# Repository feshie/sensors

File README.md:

sensors
=======
These feshie smarft sensors use an MCU (AVR) to interface to the actual sensors - and provide protocol buffer formatted data

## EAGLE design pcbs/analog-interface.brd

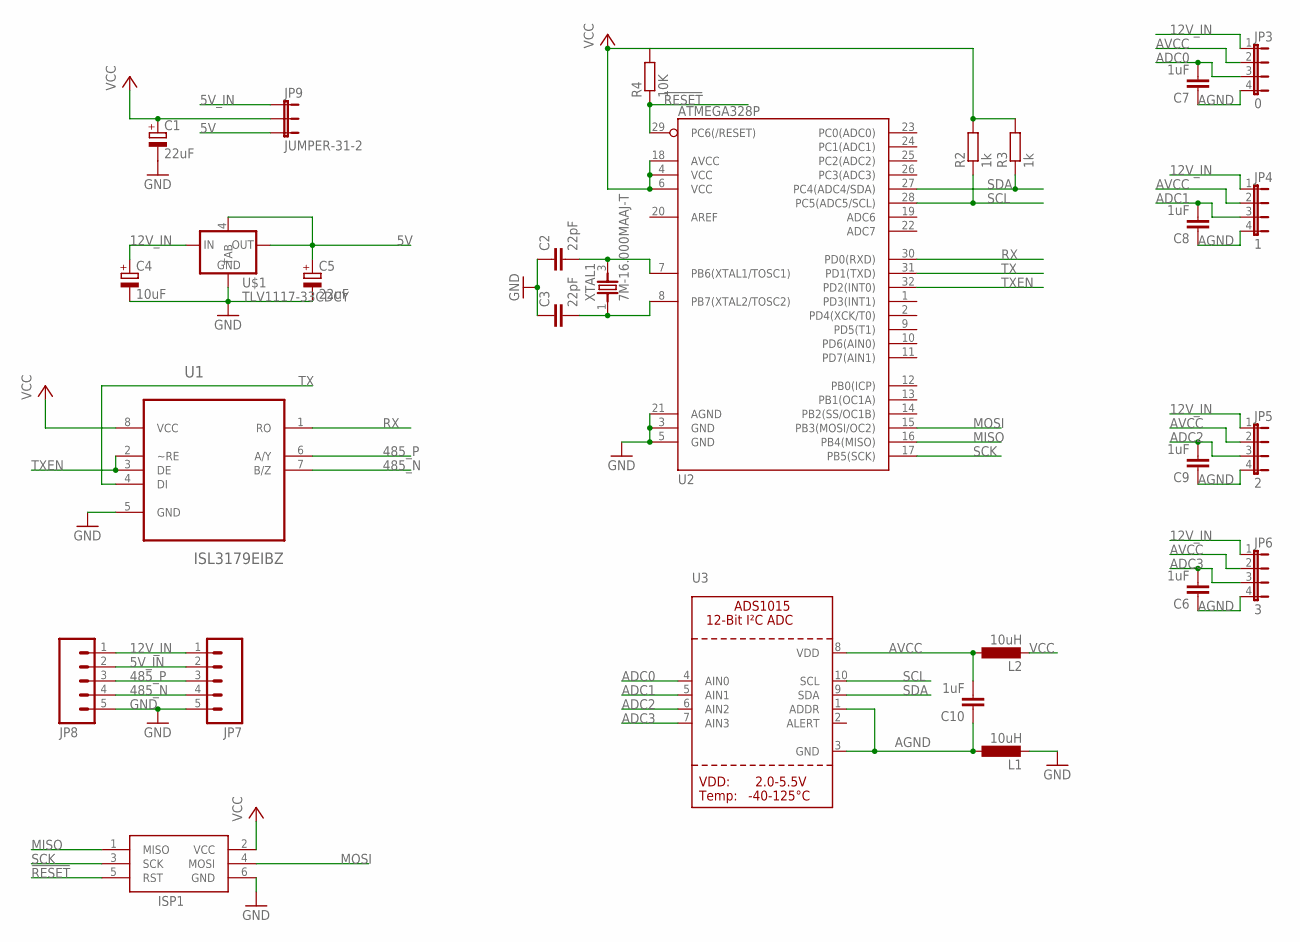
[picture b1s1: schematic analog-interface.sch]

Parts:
C1, C5: 22uF; A/3216-18R
C2, C3: 22pF; C0805
C4: 10uF; A/3216-18R
C6, C7, C8, C9, C10: 1uF; C0805
ISP1: AVRISP-6; AVRISP
JP3: 0; JP4
JP4: 1; JP4
JP5: 2; JP4
JP6: 3; JP4
JP7, JP8: M05PTH; 1X05
JP9: JUMPER-31-2; SJ_3_PASTE1&2
L1, L2: 10uH; L3216C
R2, R3: 1k; R0805
R4: 10K; R0805
U1: ISL3179EIBZ; SOIC127P600X175-8N
U2: ATMEGA328P; TQFP32-08
U3: ADC_ADS1015; MSOP10
U$1: TLV1117-33CDCY; SOT223
XTAL1: 7M-16.000MAAJ-T; TXC_7M-16.000MAAJ-T

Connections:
5V: C5.+, JP9.3, U$1.2 (OUT), U$1.4 (TAB)
5V_IN: JP7.2, JP8.2, JP9.1
12V_IN: C4.+, JP3.1, JP4.1, JP5.1, JP6.1, JP7.1, JP8.1, U$1.3 (IN)
485_N: JP7.4, JP8.4, U1.7 (B/Z)
485_P: JP7.3, JP8.3, U1.6 (A/Y)
!RESET: ISP1.5 (RST), R4.1, U2.29 (PC6(/RESET))
ADC0: C7.2, JP3.3, U3.4 (AIN0)
ADC1: C8.2, JP4.3, U3.5 (AIN1)
ADC2: C9.2, JP5.3, U3.6 (AIN2)
ADC3: C6.2, JP6.3, U3.7 (AIN3)
AGND: C6.1, C7.1, C8.1, C9.1, C10.1, JP3.4, JP4.4, JP5.4, JP6.4, L1.1, U3.1 (ADDR), U3.3 (GND)
AVCC: C10.2, JP3.2, JP4.2, JP5.2, JP6.2, L2.1, U3.8 (VDD)
GND: C1.-, C2.1, C3.1, C4.-, C5.-, ISP1.6 (GND), JP7.5, JP8.5, L1.2, U1.5 (GND), U2.3 (GND), U2.5 (GND), U2.21 (AGND), U$1.1 (GND)
MISO: ISP1.1 (MISO), U2.16 (PB4(MISO))
MOSI: ISP1.4 (MOSI), U2.15 (PB3(MOSI/OC2))
unnamed: C2.2, U2.7 (PB6(XTAL1/TOSC1)), XTAL1.3
unnamed: C3.2, U2.8 (PB7(XTAL2/TOSC2)), XTAL1.1
RX: U1.1 (RO), U2.30 (PD0(RXD))
SCK: ISP1.3 (SCK), U2.17 (PB5(SCK))
SCL: R2.1, U2.28 (PC5(ADC5/SCL)), U3.10 (SCL)
SDA: R3.1, U2.27 (PC4(ADC4/SDA)), U3.9 (SDA)
TX: U1.4 (DI), U2.31 (PD1(TXD))
TXEN: U1.2 (~RE), U1.3 (DE), U2.32 (PD2(INT0))
VCC: C1.+, ISP1.2 (VCC), JP9.2, L2.2, R2.2, R3.2, R4.2, U1.8 (VCC), U2.4 (VCC), U2.6 (VCC), U2.18 (AVCC)

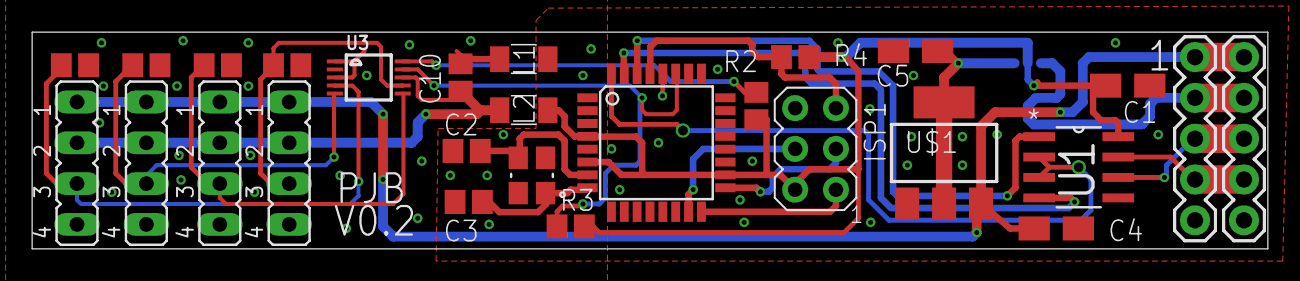
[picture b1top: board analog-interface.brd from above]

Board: 2 copper layers, 76.9 x 13.5 mm, 28 parts (1 on the bottom side), 24 nets.

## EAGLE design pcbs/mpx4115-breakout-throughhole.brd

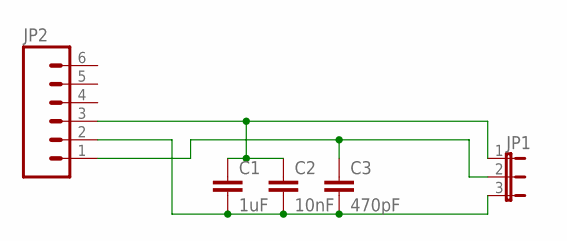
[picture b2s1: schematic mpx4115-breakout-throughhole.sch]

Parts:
C1: 1uF; C0805
C2: 10nF; C0805
C3: 470pF; C0805
JP1: JP2E; JP2
JP2: M06NO_SILK; 1X06_NO_SILK

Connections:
GND: C1.2, C2.2, C3.2, JP2.2
VCC: C1.1, C2.1, JP1.1, JP2.3
VOUT: C3.1, JP1.2, JP2.1

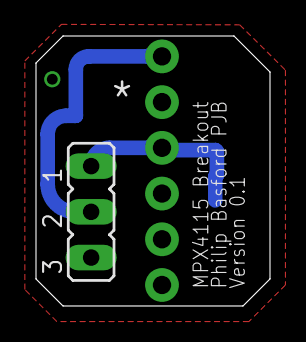
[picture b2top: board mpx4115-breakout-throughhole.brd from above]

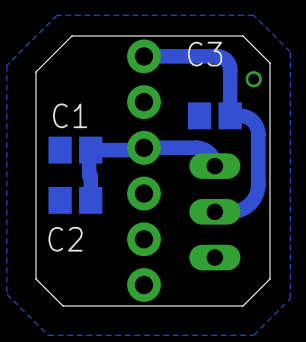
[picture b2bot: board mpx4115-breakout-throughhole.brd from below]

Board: 2 copper layers, 13.0 x 15.0 mm, 5 parts (3 on the bottom side), 3 nets.

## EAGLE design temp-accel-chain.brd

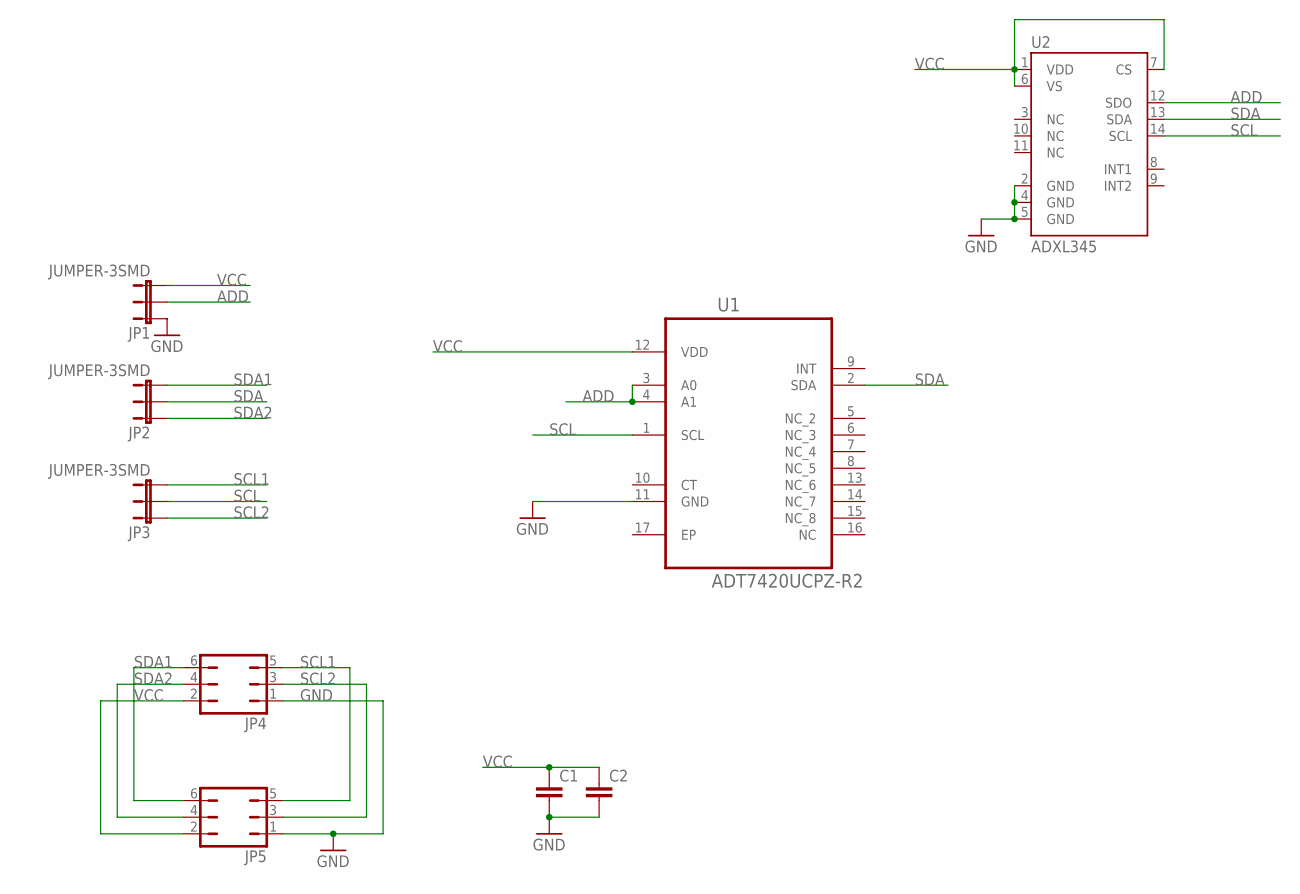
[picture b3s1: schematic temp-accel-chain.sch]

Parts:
C1, C2: C-EUC0805; C0805
JP1, JP2, JP3: JUMPER-3SMD; SJ_3
JP4, JP5: JP3Q
U1: ADT7420UCPZ-R2; QFN65P400X400X80-17N
U2: ADXL345; LGA14

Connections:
ADD: JP1.2, U1.3 (A0), U1.4 (A1), U2.12 (SDO)
GND: C1.2, C2.2, JP1.1, JP4.1, JP5.1, U1.11 (GND), U2.2 (GND), U2.4 (GND), U2.5 (GND)
SCL: JP3.2, U1.1 (SCL), U2.14 (SCL)
SCL1: JP3.3, JP4.5, JP5.5
SCL2: JP3.1, JP4.3, JP5.3
SDA: JP2.2, U1.2 (SDA), U2.13 (SDA)
SDA1: JP2.3, JP4.6, JP5.6
SDA2: JP2.1, JP4.4, JP5.4
VCC: C1.1, C2.1, JP1.3, JP4.2, JP5.2, U1.12 (VDD), U2.1 (VDD), U2.6 (VS), U2.7 (CS)

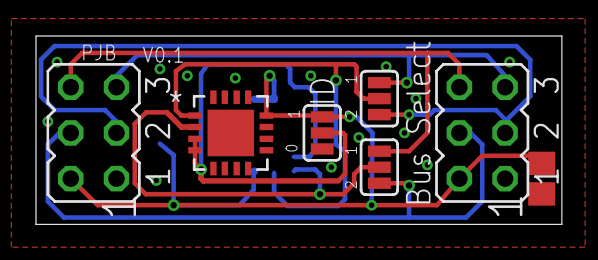
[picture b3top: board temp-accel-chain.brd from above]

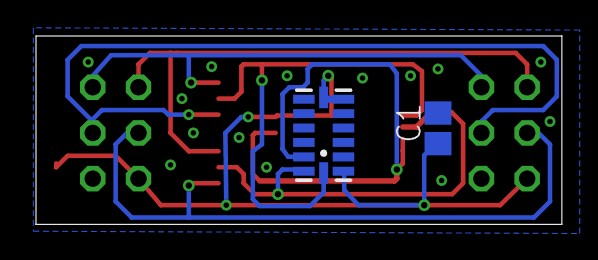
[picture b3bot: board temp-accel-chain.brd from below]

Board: 2 copper layers, 29.2 x 10.5 mm, 9 parts (2 on the bottom side), 9 nets.

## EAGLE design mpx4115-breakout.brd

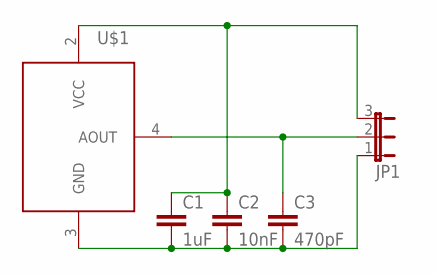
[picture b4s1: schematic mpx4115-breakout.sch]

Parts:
C1: 1uF; C0805
C2: 10nF; C0805
C3: 470pF; C0805
JP1: JP2E; JP2
U$1: MPX4115A

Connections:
AOUT: C3.1, JP1.2, U$1.4 (AOUT)
GND: C1.2, C2.2, C3.2, JP1.1, U$1.3 (GND)
VCC: C1.1, C2.1, JP1.3, U$1.2 (VCC)

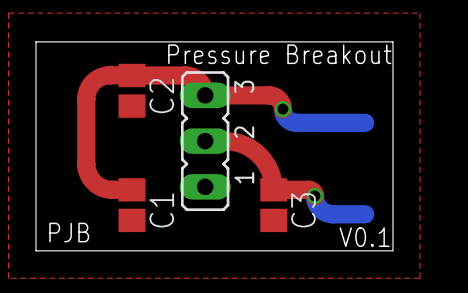
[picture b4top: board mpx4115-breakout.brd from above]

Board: 2 copper layers, 22.0 x 12.3 mm, 5 parts (1 on the bottom side), 3 nets.

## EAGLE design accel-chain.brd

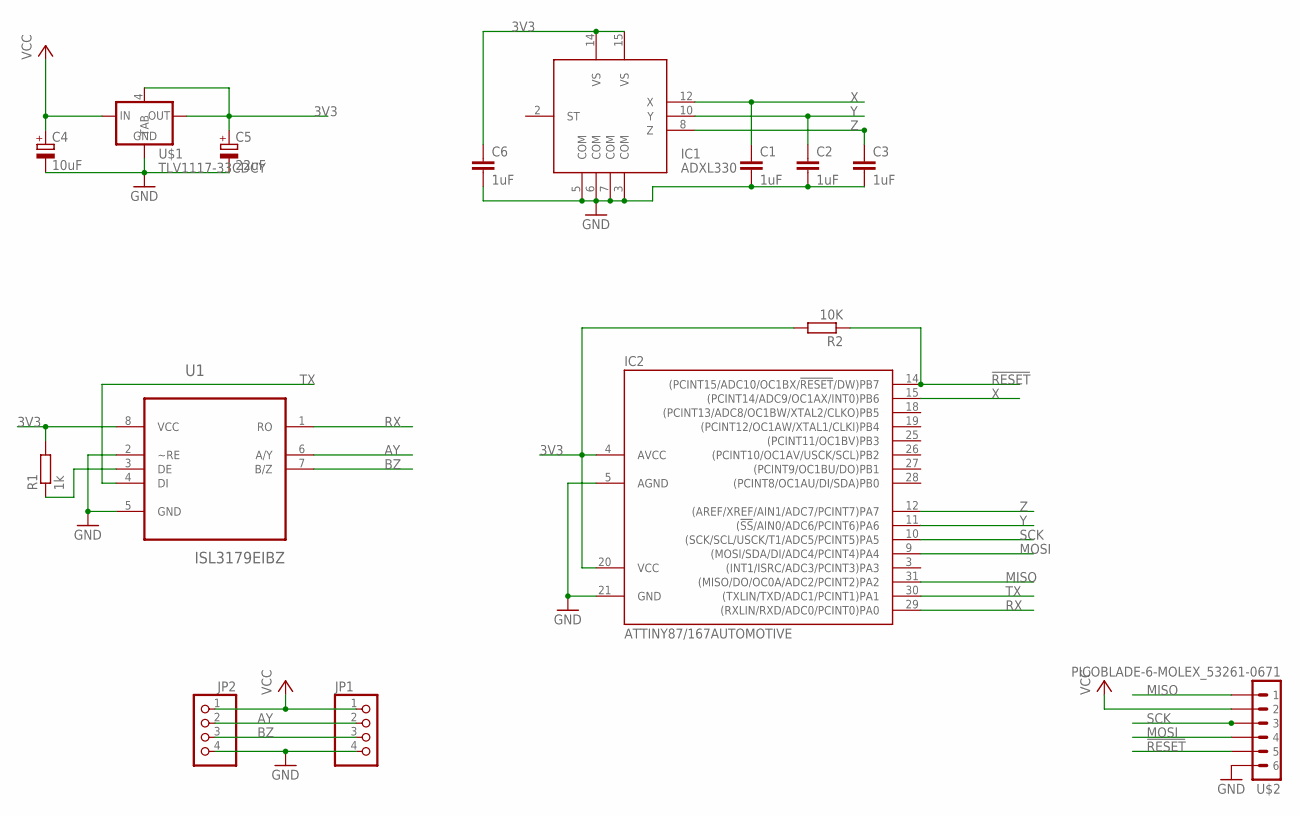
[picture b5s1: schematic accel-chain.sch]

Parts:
C1, C2, C3, C6: 1uF; C0805
C4: 10uF; A/3216-18R
C5: 22uF; A/3216-18R
IC1: ADXL330; LFCSP16
IC2: ATTINY87/167AUTOMOTIVE; MLF32
JP1, JP2: PINHD-1X4; 1X04
R1: 1k; R0805
R2: 10K; R0805
U1: ISL3179EIBZ; SOIC127P600X175-8N
U$1: TLV1117-33CDCY; SOT223
U$2: PICOBLADE-6-MOLEX_53261-0671; PICOBLADE_6-MOLEX_53261-0671

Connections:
3V3: C5.+, C6.1, IC1.14 (VS), IC1.15 (VS), IC2.4 (AVCC), IC2.20 (VCC), R1.2, R2.2, U1.8 (VCC), U$1.2 (OUT), U$1.4 (TAB)
!RESET: IC2.14 ((PCINT15/ADC10/OC1BX/!RESET!/DW)PB7), R2.1, U$2.5
AY: JP1.2, JP2.2, U1.6 (A/Y)
BZ: JP1.3, JP2.3, U1.7 (B/Z)
GND: C1.2, C2.2, C3.2, C4.-, C5.-, C6.2, IC1.3 (COM), IC1.5 (COM), IC1.6 (COM), IC1.7 (COM), IC2.5 (AGND), IC2.21 (GND), JP1.4, JP2.4, U1.2 (~RE), U1.5 (GND), U$1.1 (GND), U$2.6
MISO: IC2.31 ((MISO/DO/OC0A/ADC2/PCINT2)PA2), U$2.1
MOSI: IC2.9 ((MOSI/SDA/DI/ADC4/PCINT4)PA4), U$2.4
unnamed: R1.1, U1.3 (DE)
RX: IC2.29 ((RXLIN/RXD/ADC0/PCINT0)PA0), U1.1 (RO)
SCK: IC2.10 ((SCK/SCL/USCK/T1/ADC5/PCINT5)PA5), U$2.3
TX: IC2.30 ((TXLIN/TXD/ADC1/PCINT1)PA1), U1.4 (DI)
VCC: C4.+, JP1.1, JP2.1, U$1.3 (IN), U$2.2
X: C1.1, IC1.12 (X), IC2.15 ((PCINT14/ADC9/OC1AX/INT0)PB6)
Y: C2.1, IC1.10 (Y), IC2.11 ((!SS!/AIN0/ADC6/PCINT6)PA6)
Z: C3.1, IC1.8 (Z), IC2.12 ((AREF/XREF/AIN1/ADC7/PCINT7)PA7)

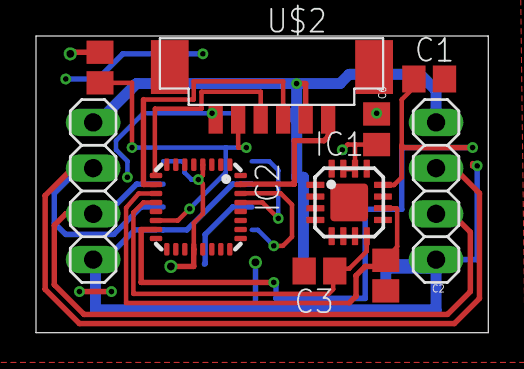
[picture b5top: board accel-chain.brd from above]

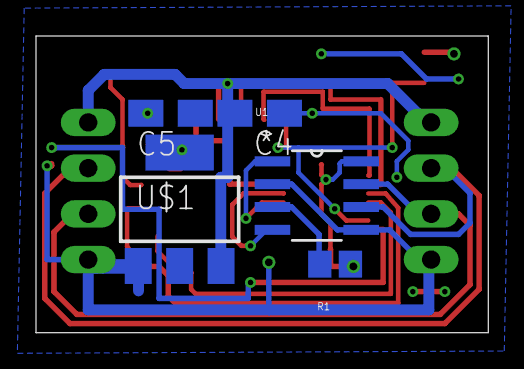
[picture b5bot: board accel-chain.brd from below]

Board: 2 copper layers, 25.1 x 16.5 mm, 15 parts (5 on the bottom side), 15 nets.

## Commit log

2014-05-12 A board for the accel chain
2014-05-13 Now with picoblade connectors
2014-05-16 a board containing an avr, programming header, rs485 driver. The I2C and 1W ports are broken out to headers making this suitable for the head of a chain
2014-05-16 forgot i2c pullups
2014-05-17 now uses an avr supported by arduino
2014-06-08 added optional 3v3 reg
2014-06-09 first version - no accel
2014-06-09 silk screen worked on. drc fixed
2014-06-09 now has 2 I2C busses
2014-06-09 added 10ks to adress lines
2014-06-10 temp i2c address either 00 or 11 thus saving a resistor
2014-06-10 extended ground plane out
2014-06-11 added accel to back and mostly routed
2014-06-11 completely routed board
2014-06-11 renumbered
2014-06-11 more silk screen stuff
2014-06-11 breakout board for mpx4115 sensor with conditioning caps as reconmended in datasheet
2014-06-12 Minor layout tweaks
2014-06-12 now called D-interface for digital
2014-06-12 removed unneeded resistor on add select pins
2014-06-12 first thoughts for analog interface board
2014-06-18 track lengths now within 0.2% for rs485
2014-06-18 done a lot of routing added vref chip
2014-06-19 Minor DRC fixes
2014-06-19 more minor DRC fixes
2014-06-19 Moved PCBs into sub folder
2014-06-19 added pull up to 1w
2014-06-19 The ds18b20 example works
2014-06-19 A better library found
2014-06-19 Will loop through and print the 1w temperature
2014-06-19 Now set up so that it can read through all devices by calling read_1W()
2014-06-20 minor changes to silk screen
2014-06-23 stubs to test individual sensors
2014-06-23 laser width set
2014-06-23 simple stub
2014-06-24 working stub, need tidying
2014-06-24 a bit more modular - still more work to do
2014-06-24 now has both addresses
2014-06-24 Accel reading using software I2C now works
2014-06-24 Added software I2C library
2014-06-24 Now uses external ADC and is long and thin. Possibly too long...
2014-06-25 Now has seperate AGND and AVCC 12V available on ADC headers lots of vias A bit shorter
2014-06-25 Added a couple of vias and Silk screen layer
2014-06-25 Now reads the temperature using the software I2C library
2014-06-25 no need for start and end tranmission when reading
2014-06-25 doesn't need wire.h general tidyage
2014-06-25 Start of combining the stubs
2014-06-25 Pull ups added to I2C
2014-06-30 first version of through hole mpx breakout
2014-07-01 added another library for ads115 functionality
2014-07-01 now with 6 holes for pressure sensor
2014-07-01 simple stub file to show basics of reading a single ended ADC chanel
2014-07-02 Silk screen stuff
2014-07-10 cutter width set to size of lazer cutter
2014-07-15 minor changes now uses last byte as ID
2014-07-15 Added include for protocol buffers
2014-07-15 Included from tarball as their git doesn't tag the git and we don't want bleeding edge. This is 0.2.8
2014-07-16 Code to set and readback the permenant value of the ID
2014-07-24 Now reads 2 sensors
2014-07-31 Will print out a line containing all data from the chain
2014-08-02 update order
2014-08-02 adding protocol buffer encoding
2014-08-02 Starting to work on final AVR sensor driver code
2014-08-02 remove file
2014-08-02 formatting
2014-08-02 add introspection
2014-08-03 update design spec to have a more clear framing format
2014-08-04 more implementation of the serial protocol. some code tidying/refactoring
2014-08-04 introspection support
2014-08-04 docs
2014-08-10 Now also supports OW temperature spider
2014-09-02 ASCII table which loops forever and has the required pin for the RS485 command
2014-09-02 Now also prints the mode out
2014-09-02 Now uses more definitions from sensors.h
2014-09-02 debug output enabled now uses pin to control rs485
2014-09-02 Now supports spider too
2014-09-02 Now has pin for rs485 tx enable
2014-09-02 now has control of rx as well
2014-09-02 Now has control of Tx/Rx for RS485 chip
2014-09-02 Fixes #1 on both boards and version number updated
2014-09-03 now loops infinitely
2014-09-03 now uses latest submodule
2014-10-05 Now goes back to start of printable characters rather than 0
2014-10-05 Adding full files rather than symlinks for cross platform compatability. These should very rarely if not never change
2014-10-05 Now prints out in hex
2014-10-05 Now prints ID in hex
2014-10-08 sets the fuse so that the id persists between burnings
2014-10-08 here so that it's cross platform rather than symlinks
2014-10-08 Now has ADC for water pressure integrated
2014-10-08 Now toggles rs485 enable pin
2014-10-10 now outputs pressue
2014-10-10 now with tweaked offsets
2015-02-06 trying to fix symlinks
2015-02-06 removing more synlinks
2015-02-06 actual files hopefully not symlinked
2015-02-09 removed symlinks
2015-02-09 Now real files
2016-07-01 edited to make it less specific to Z1 - now nodes
2016-07-01 just moved comment to the top
2016-07-01 description comment
2016-07-01 more info

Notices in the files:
parts and their libraries:
SparkFun-DigitalIC: Licensing: Creative Commons ShareAlike 4.0 International - https://creativecommons.org/licenses/by-sa/4.0
microbuilder: This work is placed in the public domain, and may be freely used for commercial and non-commercial work with the following conditions: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
